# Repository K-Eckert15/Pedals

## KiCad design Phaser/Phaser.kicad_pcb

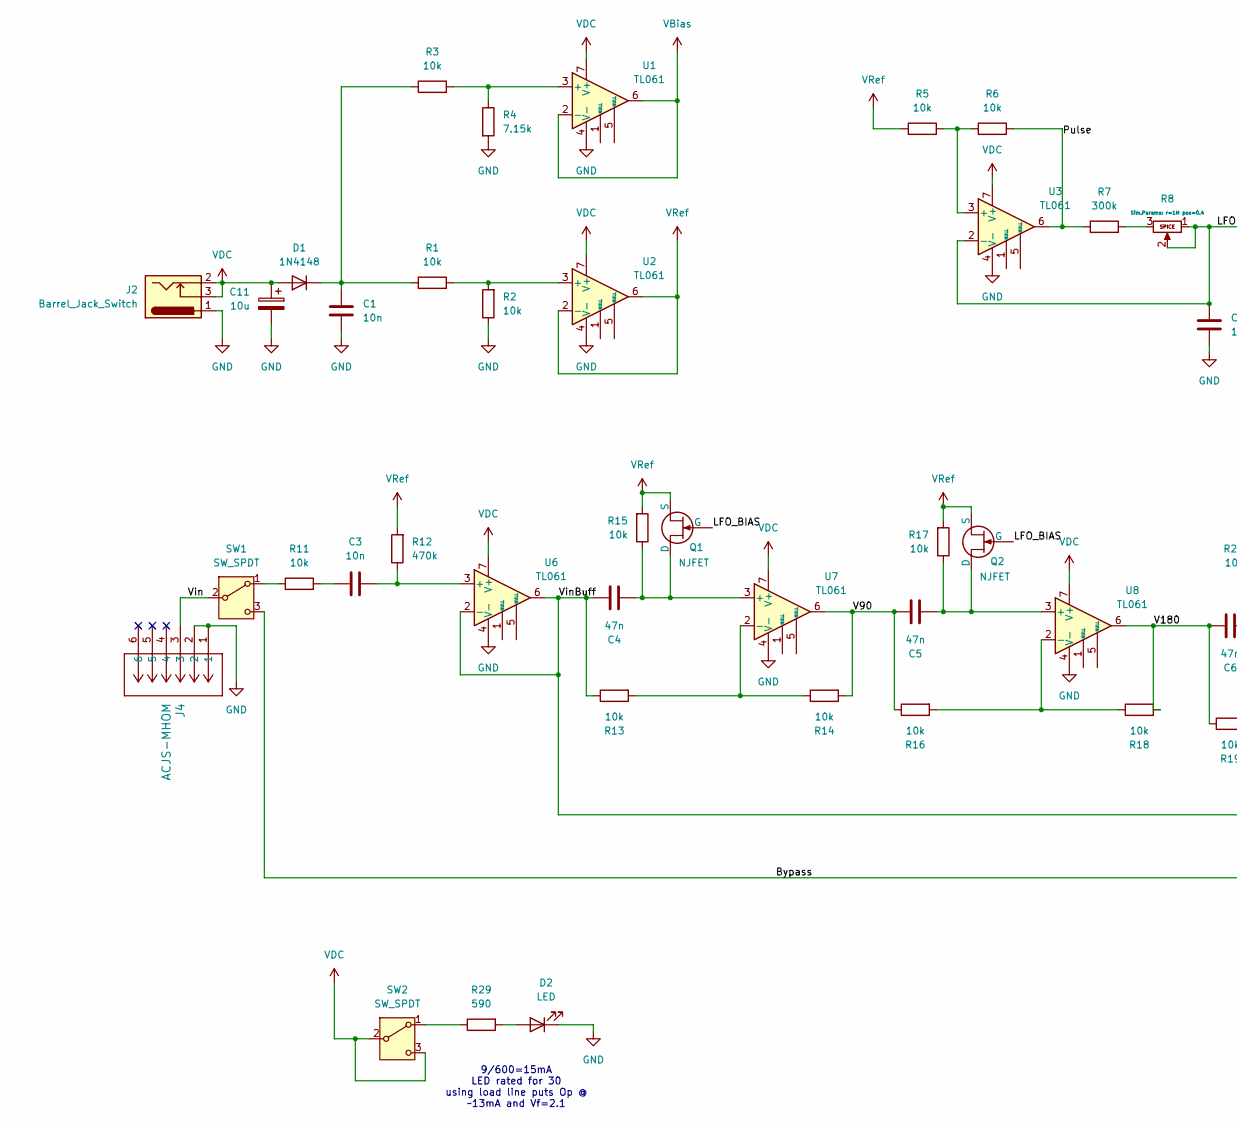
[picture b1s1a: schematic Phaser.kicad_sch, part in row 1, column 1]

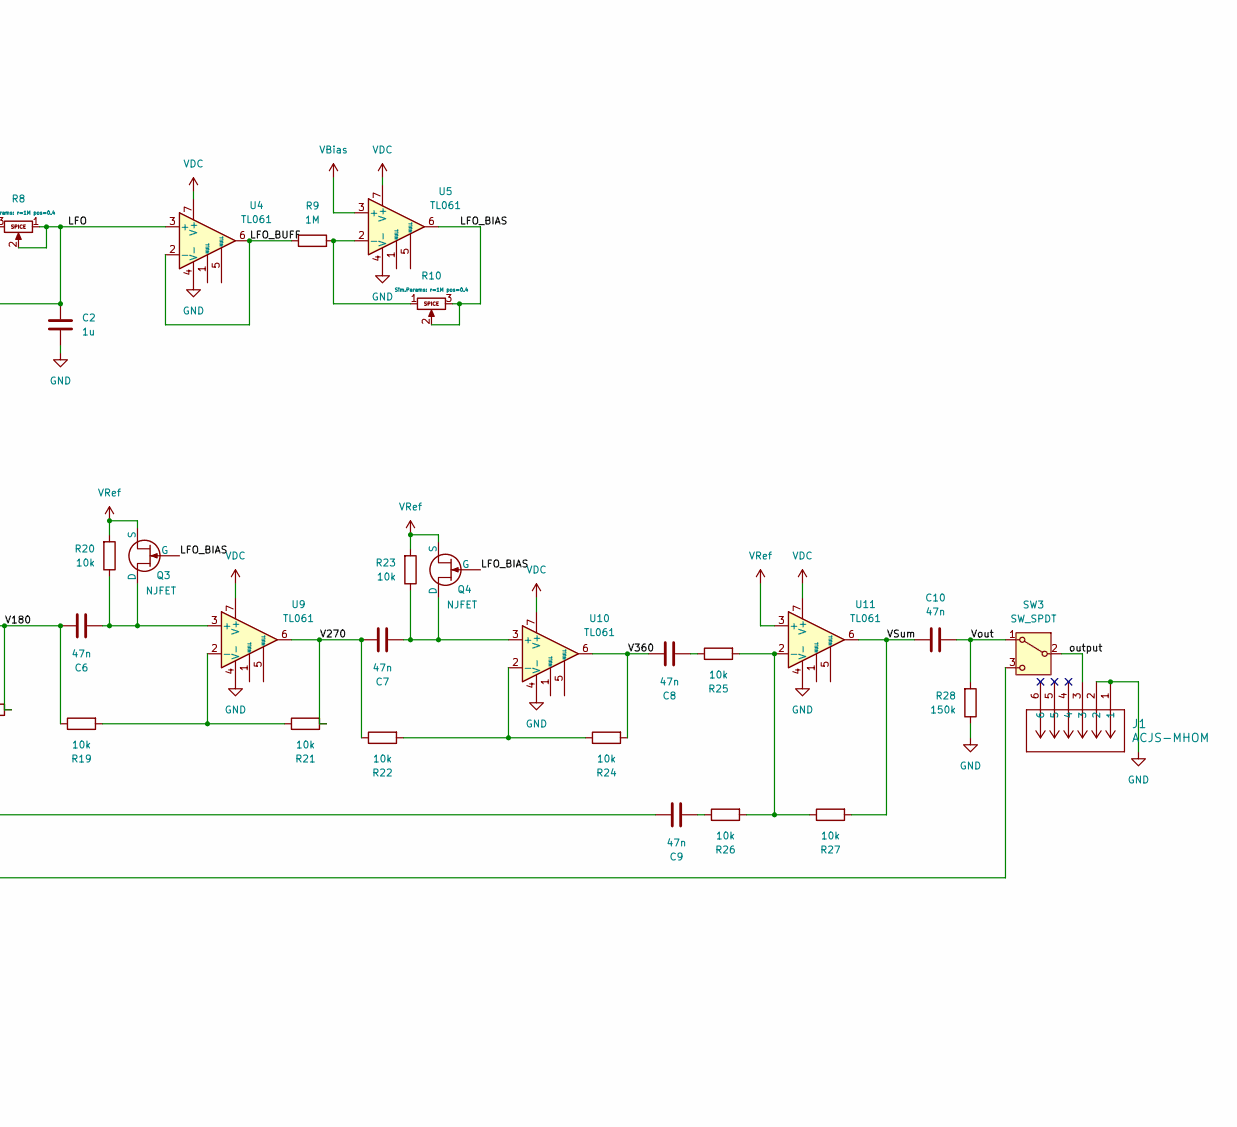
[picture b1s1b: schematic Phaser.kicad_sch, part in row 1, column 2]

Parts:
C1, C3: 10n; C_0805_2012Metric_Pad1.18x1.45mm_HandSolder; MFG # C0805C103K5RACTU
C2: 1u; C_0805_2012Metric_Pad1.18x1.45mm_HandSolder; MFG # C0805C105K3RACTU
C4, C5, C6, C7, C8, C9, C10: 47n; C_0805_2012Metric_Pad1.18x1.45mm_HandSolder; MFG # C0805C473K5RACTU
C11: 10u; CP_Radial_D10.0mm_P5.00mm; MFG # 450BXC10MEFC10X20
D1: 1N4148; D_DO-35_SOD27_P7.62mm_Horizontal; MFG # 1N4148
D2: LED; LED_D5.0mm; MFG # 151051RS11000
J1, J4: ACJS-MHOM; CONN06_JACK_ACJS_15P75X25_AMP; MFG # ACJS-MHOM
J2: Barrel_Jack_Switch; BarrelJack_GCT_DCJ200-10-A_Horizontal; MFG # PJ-002A
Q1, Q2, Q3, Q4: NJFET; TO-92; MFG # J202 TO-92 3L ROHS
R1, R2, R3, R5, R6, R11, R13, R14, R15, R16, R17, R18, R19, R20, R21, R22, R23, R24, R25, R26, R27: 10k; R_0805_2012Metric_Pad1.20x1.40mm_HandSolder; MFG # RMCF0805FT10K0
R4: 7.15k; R_0805_2012Metric_Pad1.20x1.40mm_HandSolder; MFG # ERA-6AEB7151V
R7: 300k; R_0805_2012Metric_Pad1.20x1.40mm_HandSolder; MFG # ERA-6AEB304V
R8, R10: 1M; JST_EH_B3B-EH-A_1x03_P2.50mm_Vertical; MFG # B3B-EH-A
R9: 1M; R_0805_2012Metric_Pad1.20x1.40mm_HandSolder; MFG # RG2012P-105-B-T5
R12: 470k; R_0805_2012Metric_Pad1.20x1.40mm_HandSolder; MFG # ERA-6AEB474V
R28: 150k; R_0805_2012Metric_Pad1.20x1.40mm_HandSolder; MFG # CRCW0805150KFKEA
R29: 590; R_0805_2012Metric_Pad1.20x1.40mm_HandSolder; MFG # RC0805FR-07590RL
SW1, SW2, SW3: SW_SPDT; JST_EH_B3B-EH-A_1x03_P2.50mm_Vertical; MFG # B3B-EH-A
U1, U2, U3, U4, U5, U6, U7, U8, U9, U10, U11: TL061; SOIC-8_3.9x4.9mm_P1.27mm; MFG # TL061CDR

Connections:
/Bypass: SW1.3 (C), SW3.3 (C)
/LFO: C2.1, R8.1, R8.2, U3.2 (-), U4.3 (+)
/LFO_BIAS: Q1.3 (G), Q2.3 (G), Q3.3 (G), Q4.3 (G), R10.2, R10.3, U5.6
/LFO_BUFF: R9.1, U4.2 (-), U4.6
/Pulse: R6.2, R7.1, U3.6
/V90: C5.1, R14.2, R16.1, U7.6
/V180: C6.1, R18.2, R19.1, U8.6
/V270: C7.1, R21.2, R22.1, U9.6
/V360: C8.1, R24.2, U10.6
/VSum: C10.1, R27.2, U11.6
/Vin: J4.3, SW1.2 (B)
/VinBuff: C4.1, C9.1, R13.1, U6.2 (-), U6.6
/Vout: C10.2, R28.2, SW3.1 (A)
/output: J1.3, SW3.2 (B)
GND: C1.2, C2.2, C11.2, D2.1 (K), J1.1, J1.2, J2.1, J4.1, J4.2, R2.1, R4.2, R28.1, U1.4 (V-), U2.4 (V-), U3.4 (V-), U4.4 (V-), U5.4 (V-), U6.4 (V-), U7.4 (V-), U8.4 (V-), U9.4 (V-), U10.4 (V-), U11.4 (V-)
unnamed: C3.1, R11.2
unnamed: C8.2, R25.1
unnamed: C9.2, R26.1
unnamed: C1.1, D1.1 (K), R1.1, R3.1
unnamed: D2.2 (A), R29.2
unnamed: C4.2, Q1.1 (D), R15.1, U7.3 (+)
unnamed: C5.2, Q2.1 (D), R17.1, U8.3 (+)
unnamed: C6.2, Q3.1 (D), R20.1, U9.3 (+)
unnamed: C7.2, Q4.1 (D), R23.1, U10.3 (+)
unnamed: R7.2, R8.3
unnamed: R11.1, SW1.1 (A)
unnamed: R29.1, SW2.1 (A)
unnamed: R3.2, R4.1, U1.3 (+)
unnamed: R1.2, R2.2, U2.3 (+)
unnamed: R5.2, R6.1, U3.3 (+)
unnamed: R9.2, R10.1, U5.2 (-)
unnamed: C3.2, R12.1, U6.3 (+)
unnamed: R13.2, R14.1, U7.2 (-)
unnamed: R16.2, R18.1, U8.2 (-)
unnamed: R19.2, R21.1, U9.2 (-)
unnamed: R22.2, R24.1, U10.2 (-)
unnamed: R25.2, R26.2, R27.1, U11.2 (-)
VBias: U1.2 (-), U1.6, U5.3 (+)
VDC: C11.1, D1.2 (A), J2.2, J2.3, SW2.2 (B), SW2.3 (C), U1.7 (V+), U2.7 (V+), U3.7 (V+), U4.7 (V+), U5.7 (V+), U6.7 (V+), U7.7 (V+), U8.7 (V+), U9.7 (V+), U10.7 (V+), U11.7 (V+)
VRef: Q1.2 (S), Q2.2 (S), Q3.2 (S), Q4.2 (S), R5.1, R12.2, R15.2, R17.2, R20.2, R23.2, U2.2 (-), U2.6, U11.3 (+)

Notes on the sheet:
9/600=15mA LED rated for 30 using load line puts Op @ ~13mA and Vf=2.1

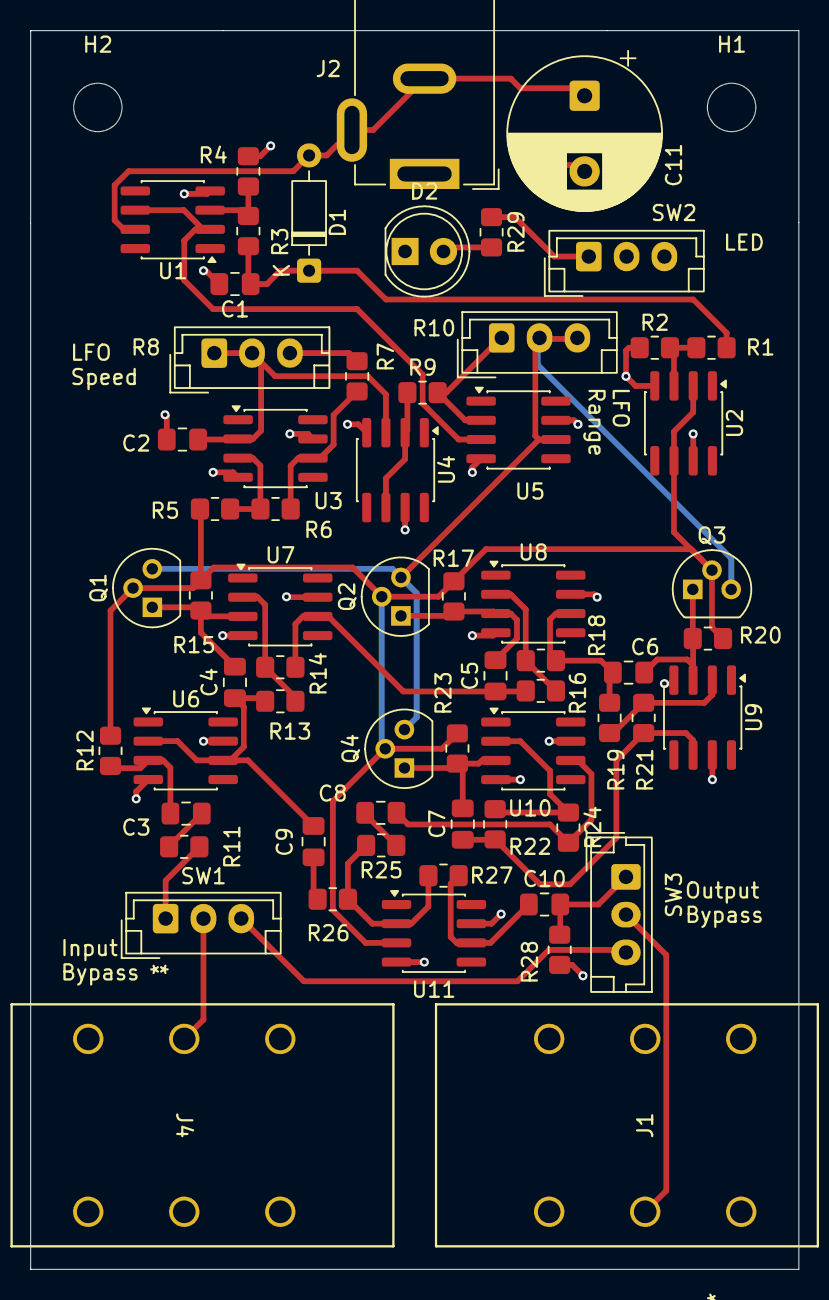
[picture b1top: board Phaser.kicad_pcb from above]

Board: 4 copper layers, 50.8 x 81.9 mm, 65 parts (0 on the bottom side), 40 nets.

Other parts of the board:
H1, H2: MountingHole; MountingHole_3.2mm_M3

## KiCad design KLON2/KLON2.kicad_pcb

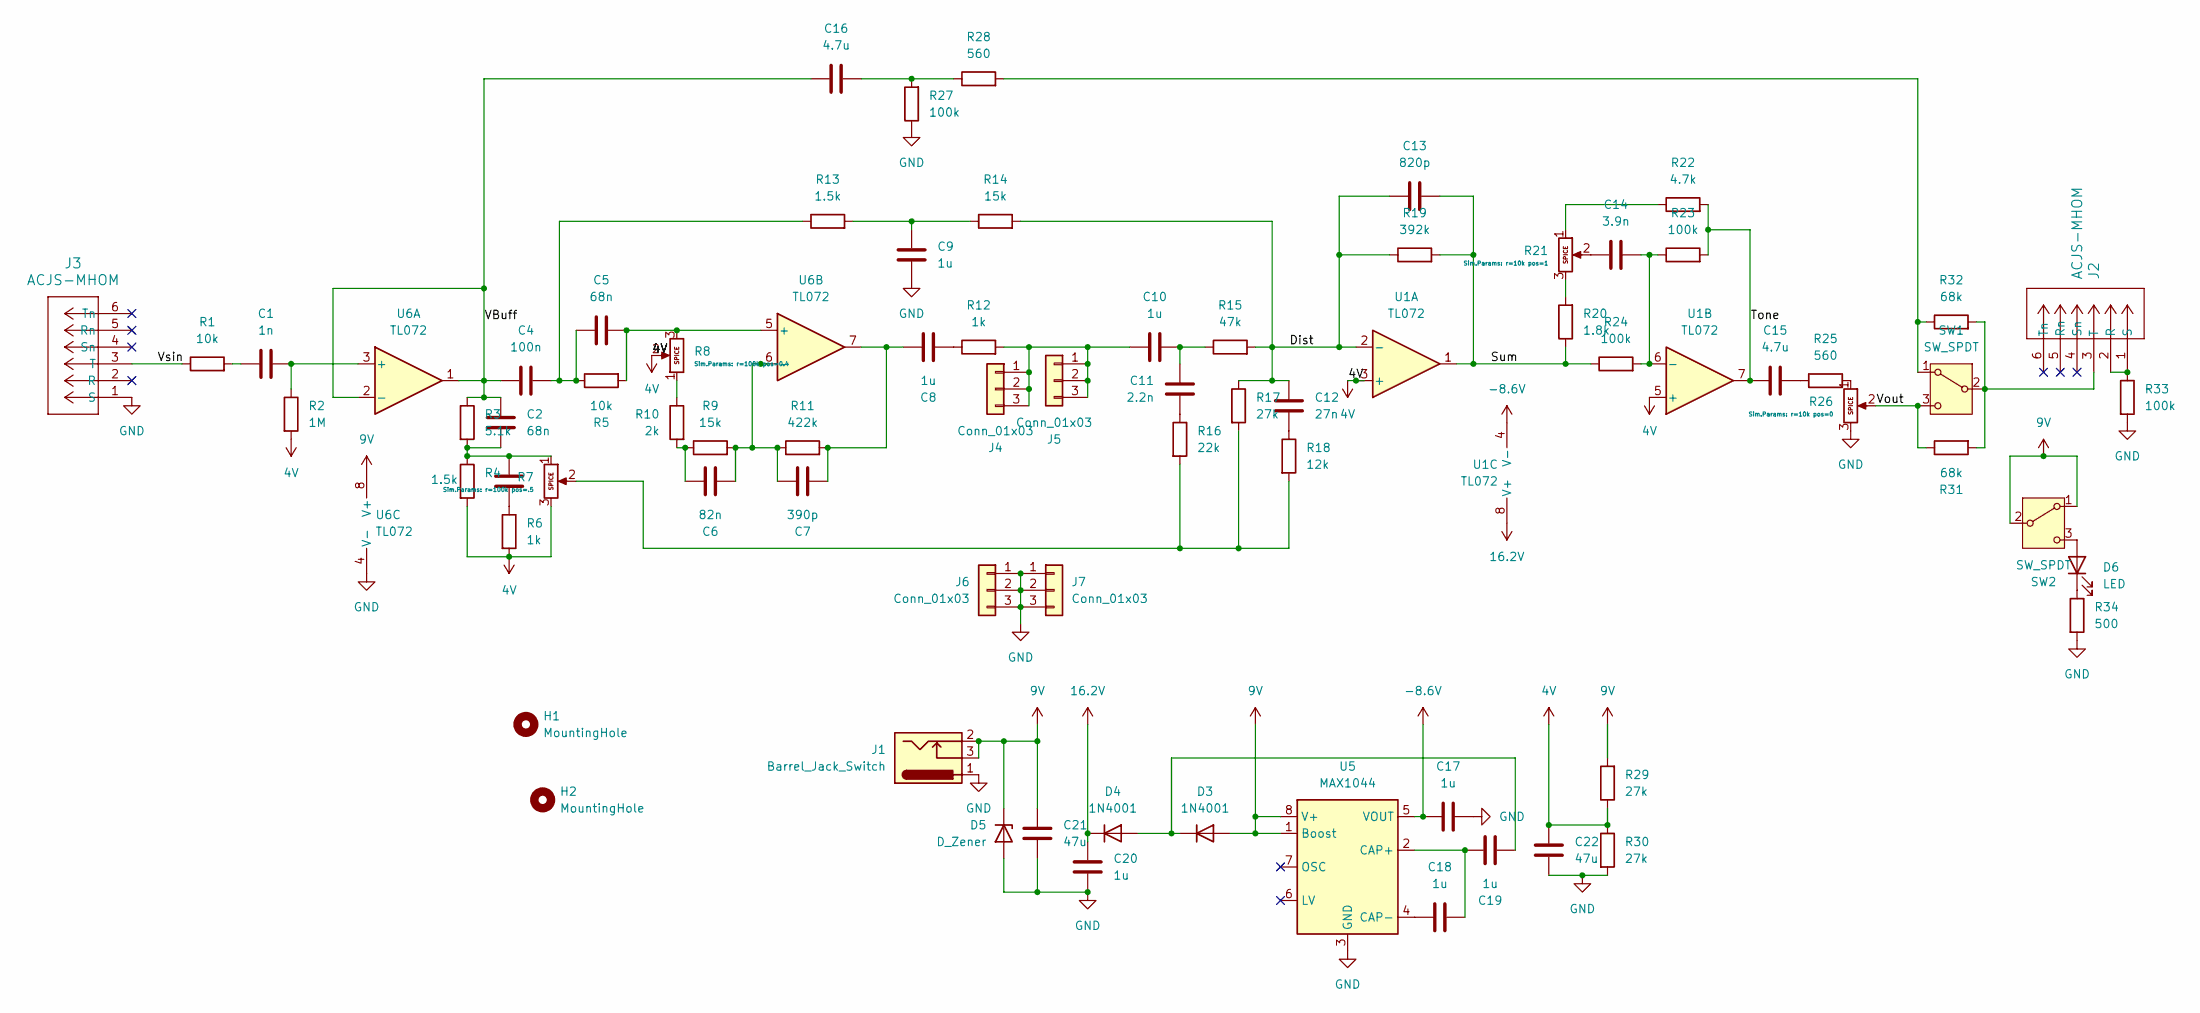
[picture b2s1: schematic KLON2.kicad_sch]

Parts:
C1: 1n; C_0805_2012Metric_Pad1.18x1.45mm_HandSolder; MFG# CL21B102KBANNNC
C2, C5: 68n; C_0805_2012Metric_Pad1.18x1.45mm_HandSolder; MFG# 885012207097
C3: 390n; C_0805_2012Metric_Pad1.18x1.45mm_HandSolder; MFG# CC0805KKX7R7BB394
C4: 100n; C_0805_2012Metric_Pad1.18x1.45mm_HandSolder; MFG# CL21B104KBCNNNC
C6: 82n; C_0805_2012Metric_Pad1.18x1.45mm_HandSolder; MFG# KGM21NR71H823KT
C7: 390p; C_0805_2012Metric_Pad1.18x1.45mm_HandSolder; MFG# CC0805JRNPO9BN391
C8, C9, C10, C17, C18, C19, C20: 1u; C_0805_2012Metric_Pad1.18x1.45mm_HandSolder; MFG# C0805C105K3RACTU
C11: 2.2n; C_0805_2012Metric_Pad1.18x1.45mm_HandSolder; MFG# C0805C222K5RACTU
C12: 27n; C_0805_2012Metric_Pad1.18x1.45mm_HandSolder; MFG# C0805C273K5RACTU
C13: 820p; C_0805_2012Metric_Pad1.18x1.45mm_HandSolder; MFG# C0805C821K3HACTU
C14: 3.9n; C_0805_2012Metric_Pad1.18x1.45mm_HandSolder; MFG# GRM2165C1H392JA01D
C15, C16: 4.7u; C_0805_2012Metric_Pad1.18x1.45mm_HandSolder; MFG# GRM21BR71C475KE51L
C21, C22: 47u; CP_Radial_D5.0mm_P2.00mm; MFG# 860020472006
D3, D4: 1N4001; D_DO-41_SOD81_P10.16mm_Horizontal; MFG# 1N4001
D5: D_Zener; D_DO-41_SOD81_P10.16mm_Horizontal; MFG# 1N4742A
D6: LED; LED_D5.0mm
H1, H2: MountingHole; MountingHole_3.2mm_M3
J1: Barrel_Jack_Switch; BarrelJack_GCT_DCJ200-10-A_Horizontal; MFG# PJ-002A
J2, J3: ACJS-MHOM; CONN06_JACK_ACJS_15P75X25_AMP; MFG# ACJS-MHOM
J4, J5, J6, J7: Conn_01x03; PinHeader_1x03_P2.54mm_Vertical
R1, R5: 10k; R_0805_2012Metric_Pad1.20x1.40mm_HandSolder; MFG# RMCF0805FT10K0
R2: 1M; R_0805_2012Metric_Pad1.20x1.40mm_HandSolder; MFG# RMCF0805FT1M00
R3: 5.1k; R_0805_2012Metric_Pad1.20x1.40mm_HandSolder; MFG# RMCF0805JT5K10
R4, R13: 1.5k; R_0805_2012Metric_Pad1.20x1.40mm_HandSolder; MFG# RMCF0805FT1K50
R6, R12: 1k; R_0805_2012Metric_Pad1.20x1.40mm_HandSolder; MFG# CRCW08051K00FKEA
R7, R8: Potentiometer; JST_EH_B3B-EH-A_1x03_P2.50mm_Vertical; MFG# PTN16-A100220K1B2
R9, R14: 15k; R_0805_2012Metric_Pad1.20x1.40mm_HandSolder; MFG# RMCF0805FT15K0
R10: 2k; R_0805_2012Metric_Pad1.20x1.40mm_HandSolder; MFG# RC0805FR-072KL
R11: 422k; R_0805_2012Metric_Pad1.20x1.40mm_HandSolder; MFG# CRCW0805422KFKEA
R15: 47k; R_0805_2012Metric_Pad1.20x1.40mm_HandSolder; MFG# RMCF0805FT47K0
R16: 22k; R_0805_2012Metric_Pad1.20x1.40mm_HandSolder; MFG# CRCW080522K0FKEA
R17, R29, R30: 27k; R_0805_2012Metric_Pad1.20x1.40mm_HandSolder; MFG# CRCW080527K0FKEA
R18: 12k; R_0805_2012Metric_Pad1.20x1.40mm_HandSolder; MFG# RMCF0805JT12K0
R19: 392k; R_0805_2012Metric_Pad1.20x1.40mm_HandSolder; MFG# RMCF0805FT392K
R20: 1.8k; R_0805_2012Metric_Pad1.20x1.40mm_HandSolder; MFG# RMCF0805JT1K80
R21: Potentiometer; JST_EH_B3B-EH-A_1x03_P2.50mm_Vertical; MFG# PTN16-D10115K1B1
R22: 4.7k; R_0805_2012Metric_Pad1.20x1.40mm_HandSolder; MFG# RMCF0805JT4K70
R23, R24, R27, R33: 100k; R_0805_2012Metric_Pad1.20x1.40mm_HandSolder; MFG# CRCW0805100KFKEA
R25, R28: 560; R_0805_2012Metric_Pad1.20x1.40mm_HandSolder; MFG# RMCF0805FT560R
R26: Potentiometer; JST_EH_B3B-EH-A_1x03_P2.50mm_Vertical; MFG# PTN16-D10120K1A1
R31, R32: 68k; R_0805_2012Metric_Pad1.20x1.40mm_HandSolder; MFG# RMCF0805JT68K0
R34: 500; R_Axial_DIN0204_L3.6mm_D1.6mm_P7.62mm_Horizontal; MFG# RNF14FBE500R
SW1, SW2: SW_SPDT; JST_EH_B3B-EH-A_1x03_P2.50mm_Vertical; MFG# B3B-EH-A
U1: TL072; SOIC-8-1EP_3.9x4.9mm_P1.27mm_EP2.29x3mm; MFG# TL072HIDR
U5: MAX1044; SOIC-8-1EP_3.9x4.9mm_P1.27mm_EP2.29x3mm; MFG# MAX1044CSA+T
U6: TL072; SOIC-8_3.9x4.9mm_P1.27mm; MFG# TL072HIDR

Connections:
4V: C22.1, R2.2, R4.2, R6.2, R7.3, R8.2, R29.1, R30.1, U1.3 (+), U1.5 (+)
9V: C21.1, D3.2 (A), D5.1 (K), J1.2, J1.3, R29.2, SW2.1 (A), SW2.2 (B), U5.1 (Boost), U5.8 (V+), U6.8 (V+)
16.2V: C20.1, D4.1 (K), U1.8 (V+)
-8.6V: C17.2, U1.4 (V-), U5.5 (VOUT)
/Dist: C12.1, C13.1, R14.2, R15.2, R17.1, R19.1, U1.2 (-)
/Sum: C13.2, R19.2, R20.1, R24.1, U1.1
/Tone: C15.1, R22.2, R23.2, U1.7
/VBuff: C2.1, C4.1, C16.1, R3.1, U6.1, U6.2 (-)
/Vout: R26.2, R31.1, SW1.3 (C)
/Vsin: J3.3 (T), R1.1
GND: C9.2, C17.1, C20.2, C21.2, C22.2, D5.2 (A), J1.1, J3.1 (S), J6.1, J6.2, J6.3, J7.1, J7.2, J7.3, R26.3, R27.1, R30.2, R33.2, R34.2, U5.3 (GND), U6.4 (V-)
unnamed: C1.1, R1.2
unnamed: C2.2, C3.1, R3.2, R4.1, R7.1
unnamed: C3.2, R6.1
unnamed: C4.2, C5.1, R5.1, R13.1
unnamed: C6.1, R9.1, R10.2
unnamed: C7.2, C8.1, R11.2, U6.7
unnamed: C8.2, R12.1
unnamed: C9.1, R13.2, R14.1
unnamed: C10.2, C11.1, R15.1
unnamed: C11.2, R16.1
unnamed: C12.2, R18.1
unnamed: C14.1, R21.2
unnamed: C15.2, R25.1
unnamed: C16.2, R27.2, R28.1
unnamed: C19.2, D3.1 (K), D4.2 (A)
unnamed: D6.2 (A), SW2.3 (C)
unnamed: D6.1 (K), R34.1
unnamed: J2.1 (S), J2.2 (R), R33.1
unnamed: J2.3 (T), R31.2, R32.2, SW1.2 (B)
unnamed: C10.1, J4.1, J4.2, J4.3, J5.1, J5.2, J5.3, R12.2
unnamed: R8.1, R10.1
unnamed: R7.2, R16.2, R17.2, R18.2
unnamed: R20.2, R21.3
unnamed: R21.1, R22.1
unnamed: R25.2, R26.1
unnamed: R28.2, R32.1, SW1.1 (A)
unnamed: C14.2, R23.1, R24.2, U1.6 (-)
unnamed: C18.2, C19.1, U5.2 (CAP+)
unnamed: C18.1, U5.4 (CAP-)
unnamed: C1.2, R2.1, U6.3 (+)
unnamed: C5.2, R5.2, R8.3, U6.5 (+)
unnamed: C6.2, C7.1, R9.2, R11.1, U6.6 (-)

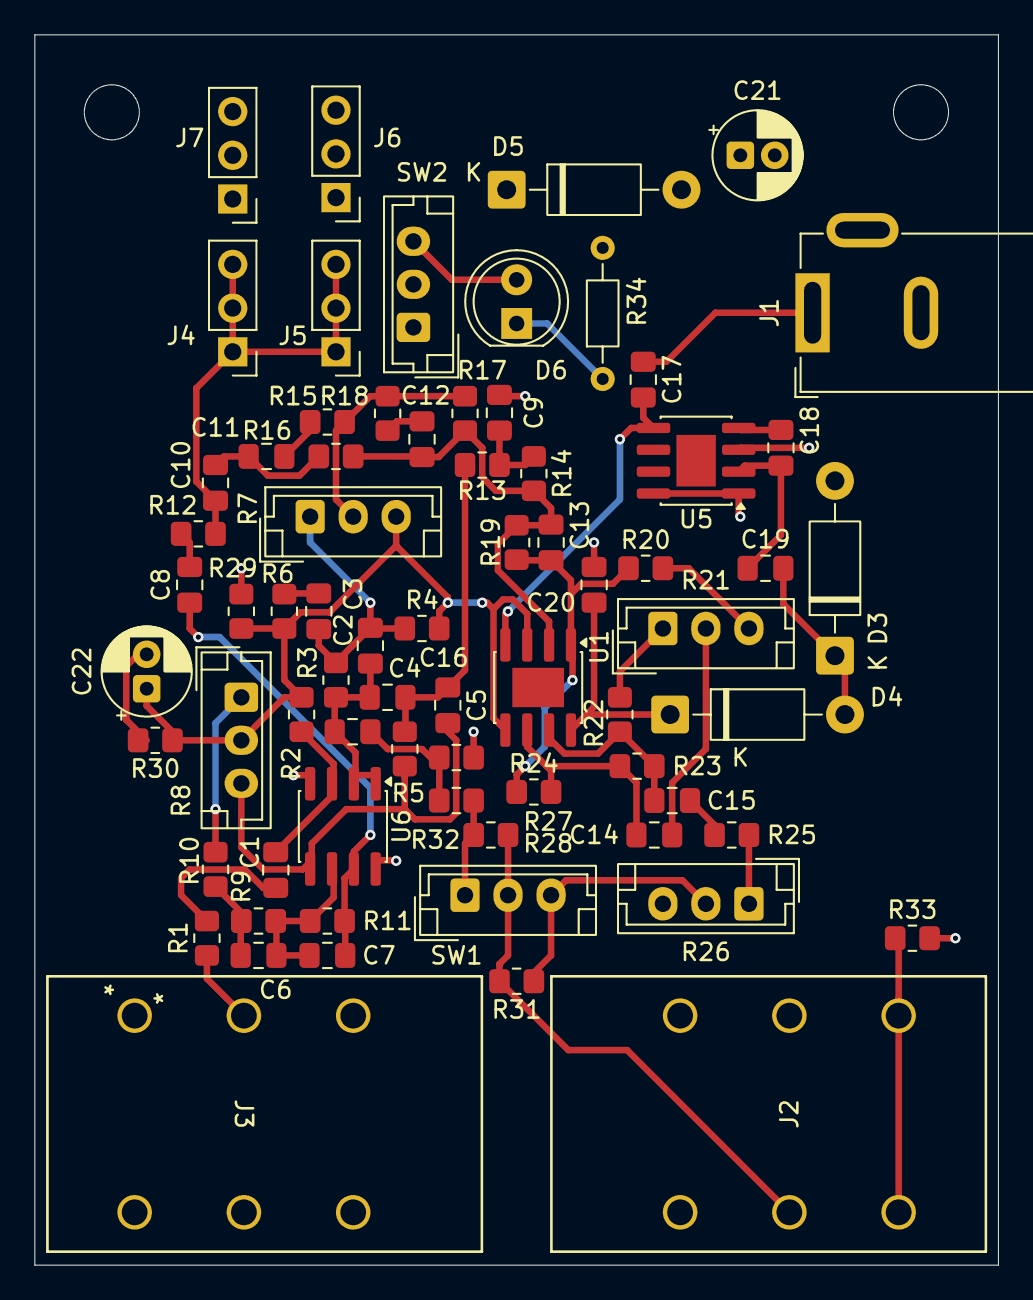
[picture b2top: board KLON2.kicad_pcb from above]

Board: 4 copper layers, 56.0 x 71.5 mm, 74 parts (0 on the bottom side), 43 nets.

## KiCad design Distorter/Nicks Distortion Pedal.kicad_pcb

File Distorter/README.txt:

Bourns PTV111-3 vertical-shaft, M9x0.75 threaded-bushing potentiometer footprint
================================================================================

Source:
  https://www.bourns.com/data/global/pdfs/PTV111.pdf
  See PTV111-3 recommended PCB layout on the second page of the PDF.

Use for all three of these PTV111-3415A series variants, subject to verification:
  RV1: PTV111-3415A-B104 100k linear
  RV2: PTV111-3415A-B103 10k linear
  RV3: PTV111-3415A-A104 100k audio

FOOTPRINT GEOMETRY (all in millimetres):
  Pin 1 x=0.0, pin 2 x=2.5, pin 3 x=5.0, dummy pin x=7.5 at y=0
  Electrical pins have 1.0 mm plated drills, 1.8 mm outer copper pads.
  Dummy pin is solderable but unnumbered because not electrically connected.
  Two 2.0 x 2.1 mm non-plated mounting slots, separated 13.0 mm.
  Mounting slots are 11.0 mm from pin row.
  Pad 2 is the wiper. Pins 1 and 3 are the resistive ends.

INSTALL (from ~/Pedals/Distorter):
  unzip PTV111_KiCad_Footprint.zip -d .

KiCad > Preferences > Manage Footprint Libraries > Project Specific Libraries:
  Nickname: Distorter
  Library path: ${KIPRJMOD}/libraries/footprints/Distorter.pretty

Then assign to RV1, RV2 and RV3:
  Distorter:Potentiometer_Bourns_PTV111-3_VerticalShaft

STEP MODEL:
  This package does NOT contain the manufacturer STEP file.
  Copy your own PTV111 STEP file to libraries/3dmodels/, open Footprint
  Editor > Footprint Properties > 3D Models, add:
  ${KIPRJMOD}/libraries/3dmodels/<your_exact_step_filename>.step
  Adjust rotation/offset to match the physical shaft and terminal holes.

IMPORTANT BEFORE FABRICATION:
  This is a datasheet-based custom footprint, not an official manufacturer EDA model.
  Verify hole position and slot sizes against the latest drawing and by printing
  a 1:1 footprint or trial fitting a physical part. Check plated vs non-plated
  slot manufacturing support at your PCB fabricator and review the KiCad 3D view.
  Do not reuse this footprint for PTV111-1, -2 or -4 layouts.

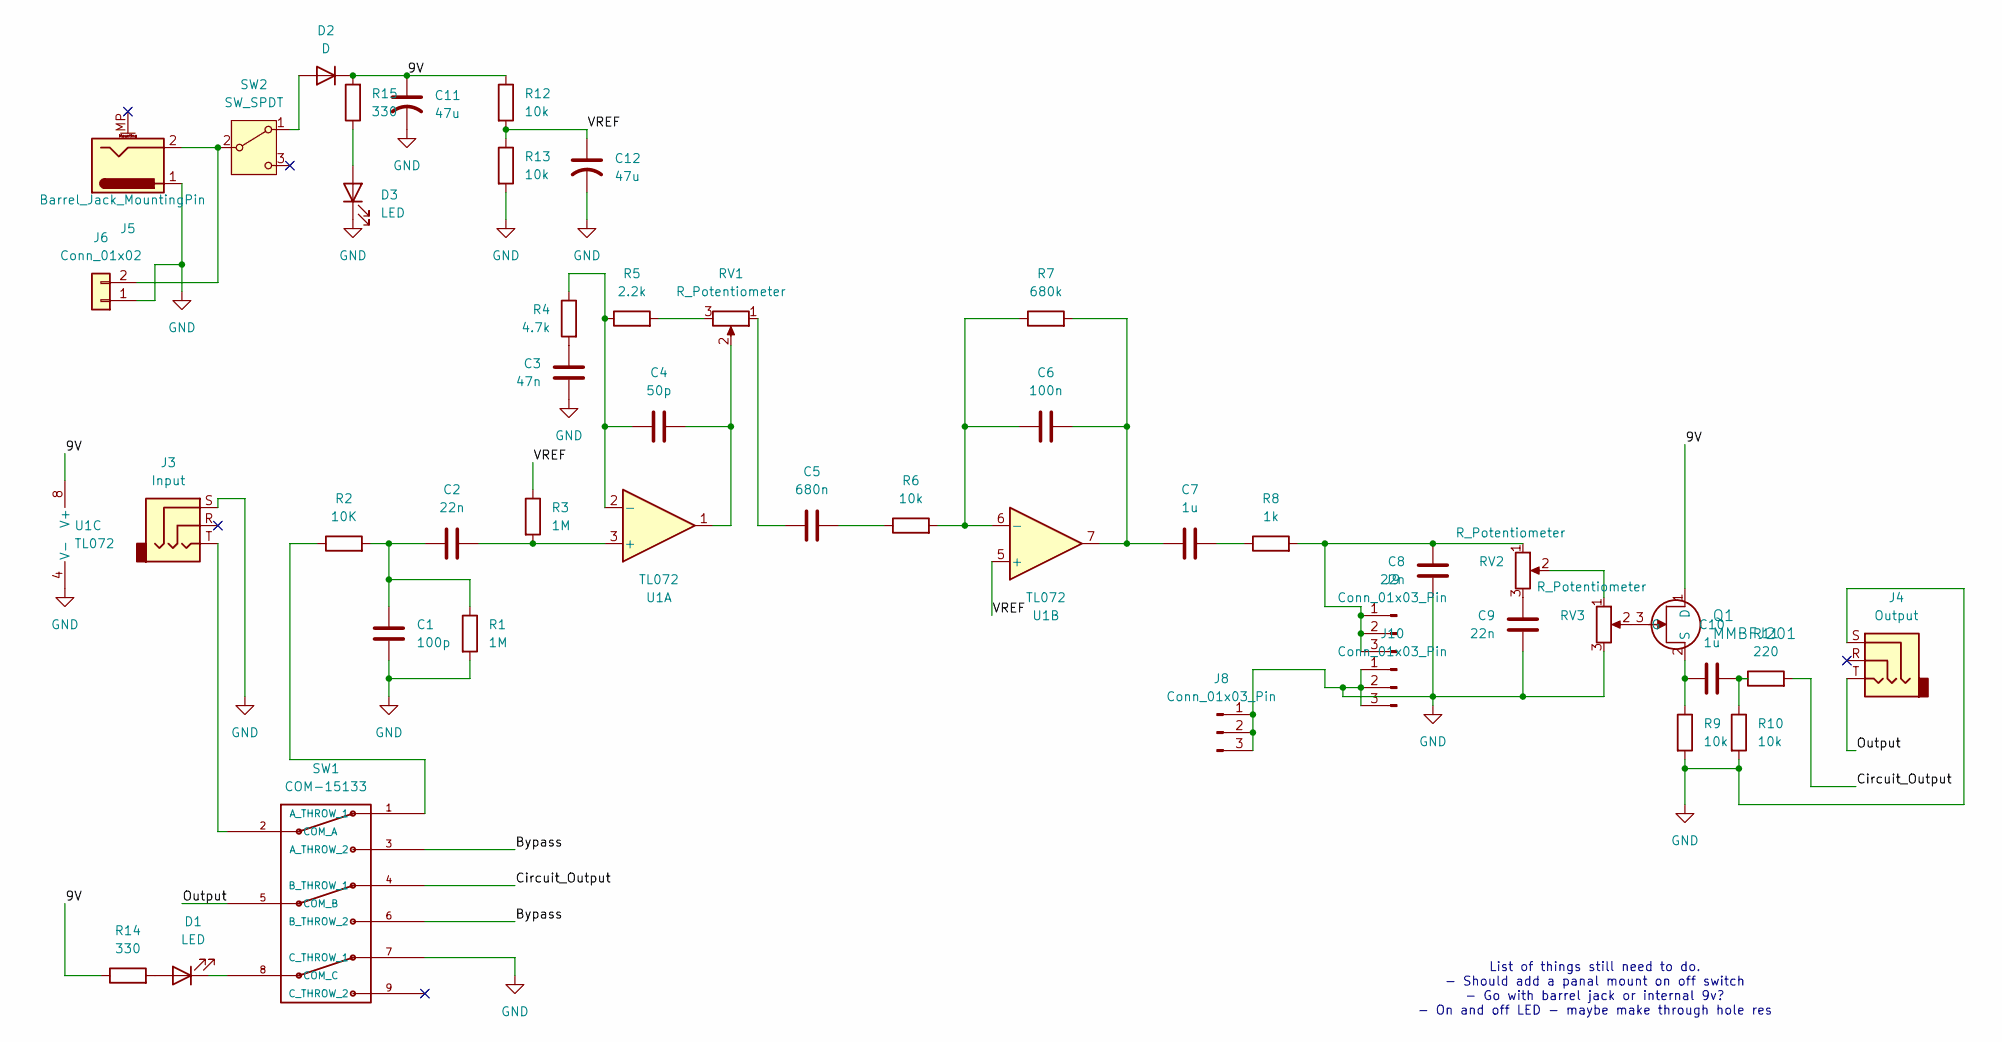
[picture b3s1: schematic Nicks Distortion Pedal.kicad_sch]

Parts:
C1: 100p; C_0805_2012Metric
C2, C8, C9: 22n; C_0805_2012Metric
C3: 47n; C_0805_2012Metric
C4: 50p; C_0805_2012Metric
C5: 680n; C_0805_2012Metric
C6: 100n; C_0805_2012Metric
C7, C10: 1u; C_0805_2012Metric
C11, C12: 47u; CP_Radial_D5.0mm_P2.00mm
D1, D3: LED; LED_D3.0mm
D2: D; D_0805_2012Metric
J3: Input; Jack_6.35mm_Neutrik_NRJ6HF-1_Horizontal
J4: Output; Jack_6.35mm_Neutrik_NRJ6HF-1_Horizontal
J5: Barrel_Jack_MountingPin; BarrelJack_CUI_PJ-063AH_Horizontal
J6: Conn_01x02; JST_EH_B2B-EH-A_1x02_P2.50mm_Vertical
J8, J9, J10: Conn_01x03_Pin; PinHeader_1x03_P2.54mm_Vertical
Q1: MMBFJ201; SOT-23
R1, R3: 1M; R_0805_2012Metric
R2: 10K; R_0805_2012Metric
R4: 4.7k; R_0805_2012Metric
R5: 2.2k; R_0805_2012Metric
R6, R9, R10, R12, R13: 10k; R_0805_2012Metric
R7: 680k; R_0805_2012Metric
R8: 1k; R_0805_2012Metric
R11: 220; R_0805_2012Metric
R14, R15: 330; R_0805_2012Metric
RV1, RV2, RV3: R_Potentiometer; Potentiometer_Bourns_PTV111-3_VerticalShaft
SW1: COM-15133; PinHeader_1x09_P2.54mm_Vertical
SW2: SW_SPDT; PinHeader_1x02_P2.54mm_Vertical
U1: TL072; SOIC-8_3.9x4.9mm_P1.27mm

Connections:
/9V: C11.1, D2.1 (K), Q1.1 (D), R12.1, R14.1, R15.2, U1.8 (V+)
/Bypass: SW1.3 (A_THROW_2), SW1.6 (B_THROW_2)
/Circuit_Output: R11.2, SW1.4 (B_THROW_1)
/Output: J4.T, SW1.5 (COM_B)
/VREF: C12.1, R3.1, R12.2, R13.1, U1.5 (+)
GND: C1.2, C3.1, C8.1, C9.1, C11.2, C12.2, D3.1 (K), J3.S, J4.S, J5.1, J6.1, J8.1, J8.2, J8.3, J10.1, J10.2, J10.3, R1.2, R9.2, R10.2, R13.2, RV3.3, SW1.7 (C_THROW_1), U1.4 (V-)
unnamed: C1.1, C2.1, R1.1, R2.2
unnamed: C3.2, R4.2
unnamed: C4.2, RV1.2, U1.1
unnamed: C5.1, RV1.1
unnamed: C5.2, R6.1
unnamed: C6.2, C7.1, R7.2, U1.7
unnamed: C7.2, R8.1
unnamed: C9.2, RV2.3
unnamed: C10.2, R10.1, R11.1
unnamed: D1.2 (A), R14.2
unnamed: D1.1 (K), SW1.8 (COM_C)
unnamed: D2.2 (A), SW2.1 (A)
unnamed: D3.2 (A), R15.1
unnamed: J5.2, J6.2, SW2.2 (B)
unnamed: C8.2, J9.1, J9.2, J9.3, R8.2, RV2.1
unnamed: Q1.3 (G), RV3.2
unnamed: C10.1, Q1.2 (S), R9.1
unnamed: R5.2, RV1.3
unnamed: RV2.2, RV3.1
unnamed: R2.1, SW1.1 (A_THROW_1)
unnamed: J3.T, SW1.2 (COM_A)
unnamed: C2.2, R3.2, U1.3 (+)
unnamed: C4.1, R4.1, R5.1, U1.2 (-)
unnamed: C6.1, R6.2, R7.1, U1.6 (-)

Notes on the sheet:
List of things still need to do. - Should add a panal mount on off switch - Go with barrel jack or internal 9v? - On and off LED - maybe make through hole res

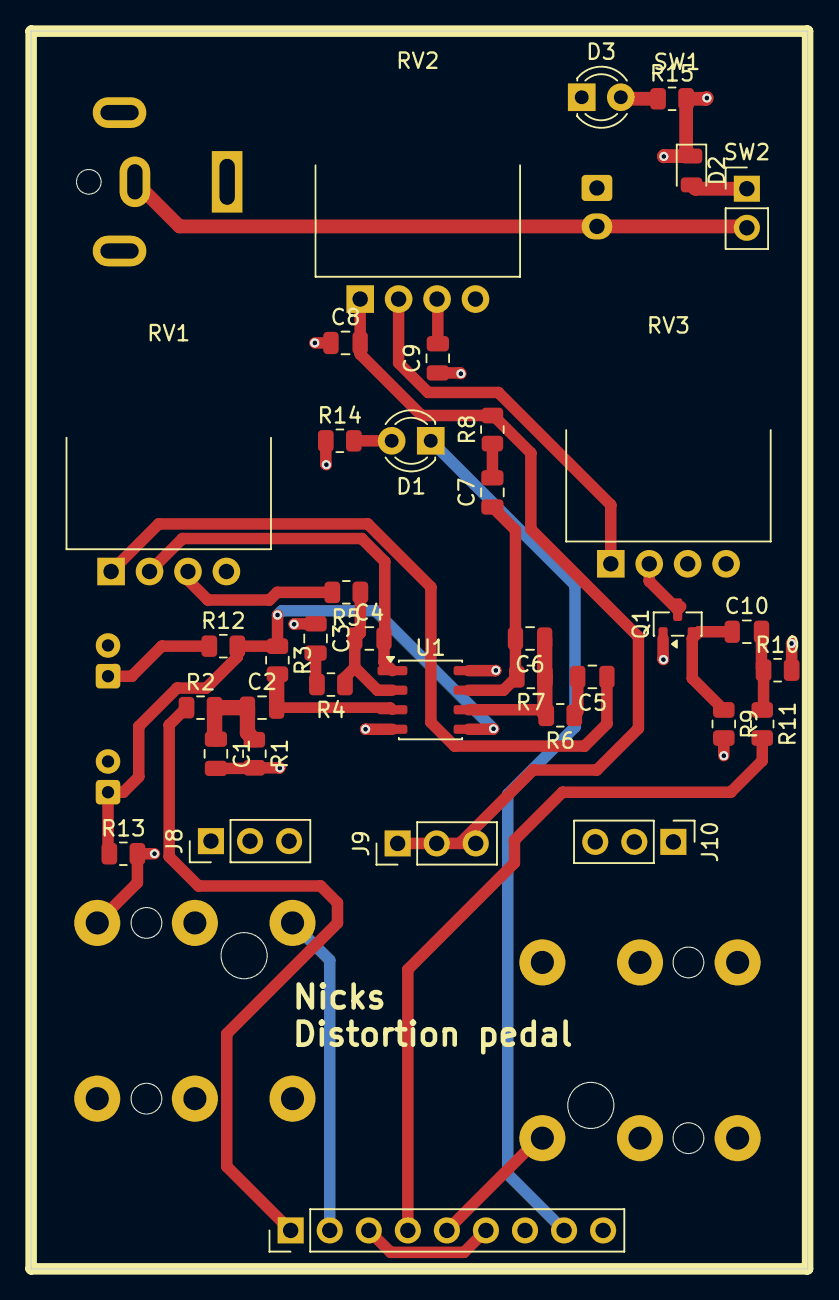
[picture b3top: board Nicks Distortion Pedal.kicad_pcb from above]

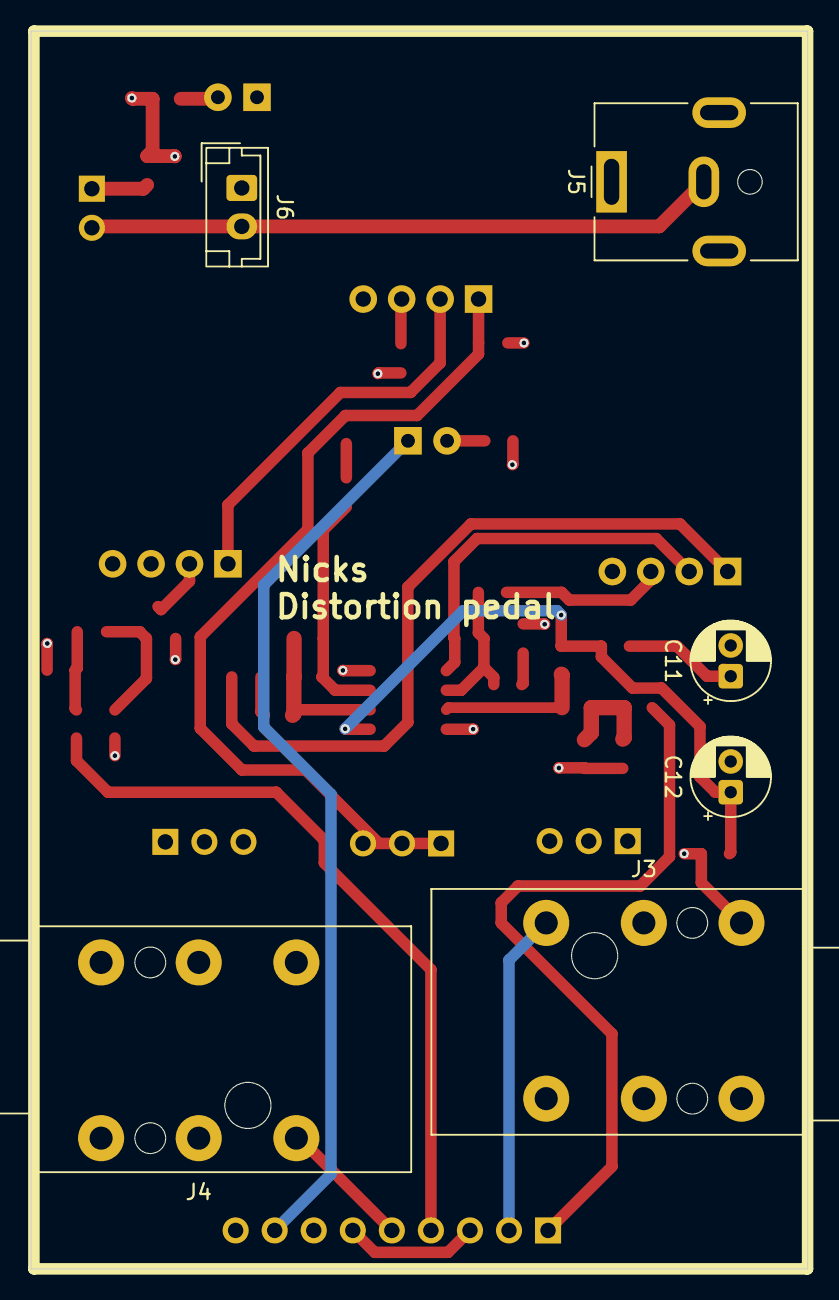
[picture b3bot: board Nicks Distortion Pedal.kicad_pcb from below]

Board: 4 copper layers, 50.5 x 80.5 mm, 44 parts (6 on the bottom side), 30 nets.
